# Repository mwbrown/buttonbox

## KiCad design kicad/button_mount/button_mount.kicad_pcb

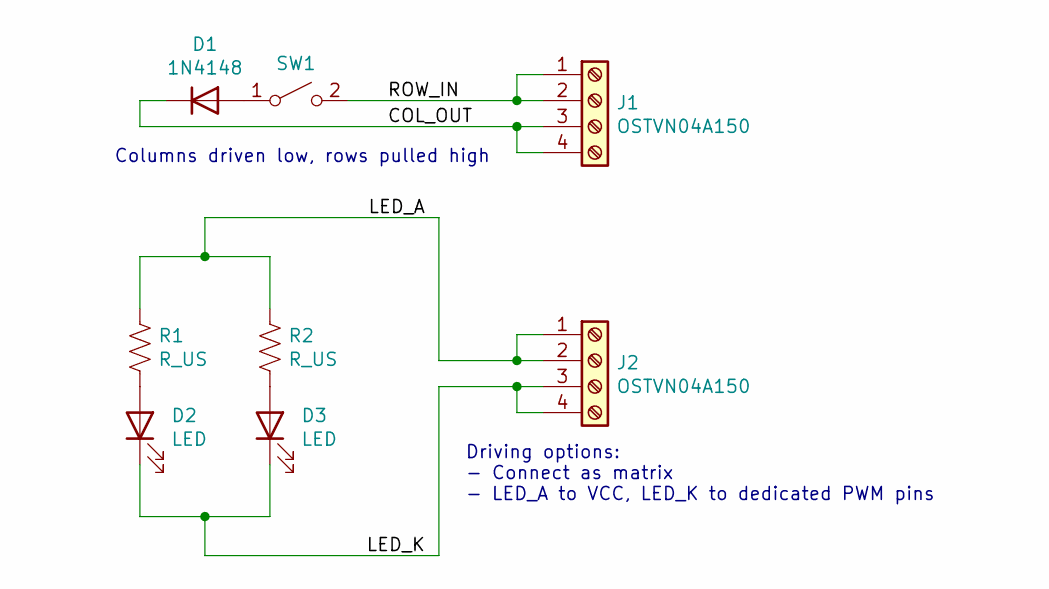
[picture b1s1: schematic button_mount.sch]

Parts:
D1: 1N4148; D_SOD-123
D2, D3: LED; LED_D3.0mm
J1, J2: OSTVN04A150
R1, R2: R_US; R_0805_HandSoldering
SW1: CROWN-SDB-201C

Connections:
/COL_OUT: D1.1 (K), J1.3, J1.4
/LED_A: J2.1, J2.2, R1.1, R2.1
/LED_K: D2.1 (K), D3.1 (K), J2.3, J2.4
/ROW_IN: J1.1, J1.2, SW1.2 (B)
unnamed: D1.2 (A), SW1.1 (A)
unnamed: D2.2 (A), R1.2
unnamed: D3.2 (A), R2.2

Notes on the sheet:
Driving options: - Connect as matrix - LED_A to VCC, LED_K to dedicated PWM pins
Columns driven low, rows pulled high

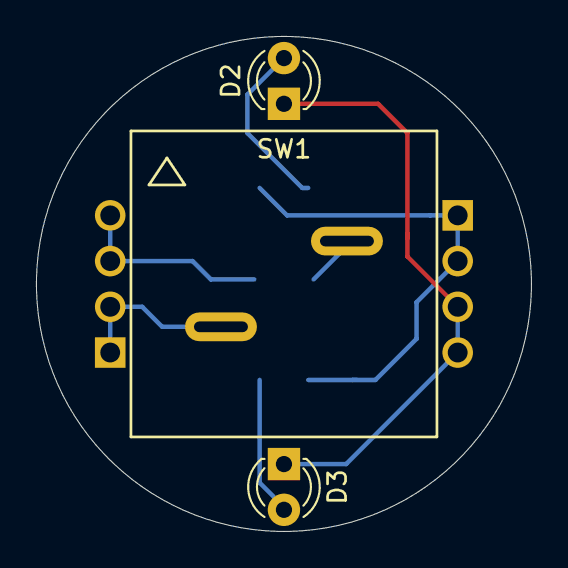
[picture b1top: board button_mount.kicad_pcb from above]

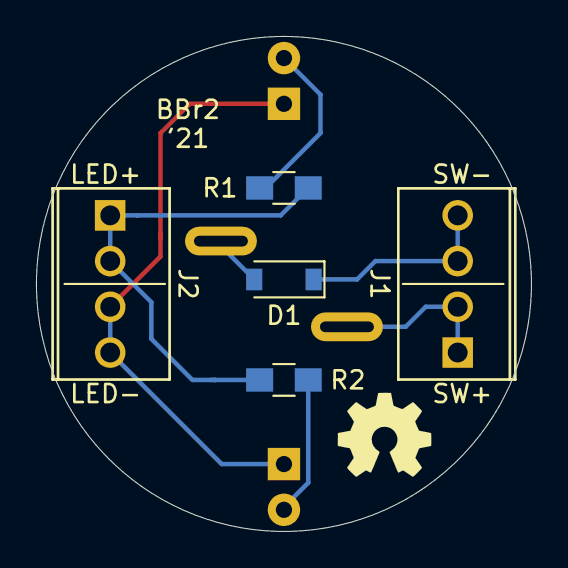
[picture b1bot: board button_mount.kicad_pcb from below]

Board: 2 copper layers, 27.5 x 27.5 mm, 8 parts (5 on the bottom side), 7 nets.

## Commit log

2021-07-05 Button mount PCB first revision
2021-07-05 Ignore kicad files
2021-07-05 Add Edge.Cuts
2021-07-05 Add more silk / OSHW logo
2021-07-05 Exported gerbers for r1 PCB order
2021-07-06 Cancelled BBr1. Updated BBr2 to include 4x term blocks, smaller diam
